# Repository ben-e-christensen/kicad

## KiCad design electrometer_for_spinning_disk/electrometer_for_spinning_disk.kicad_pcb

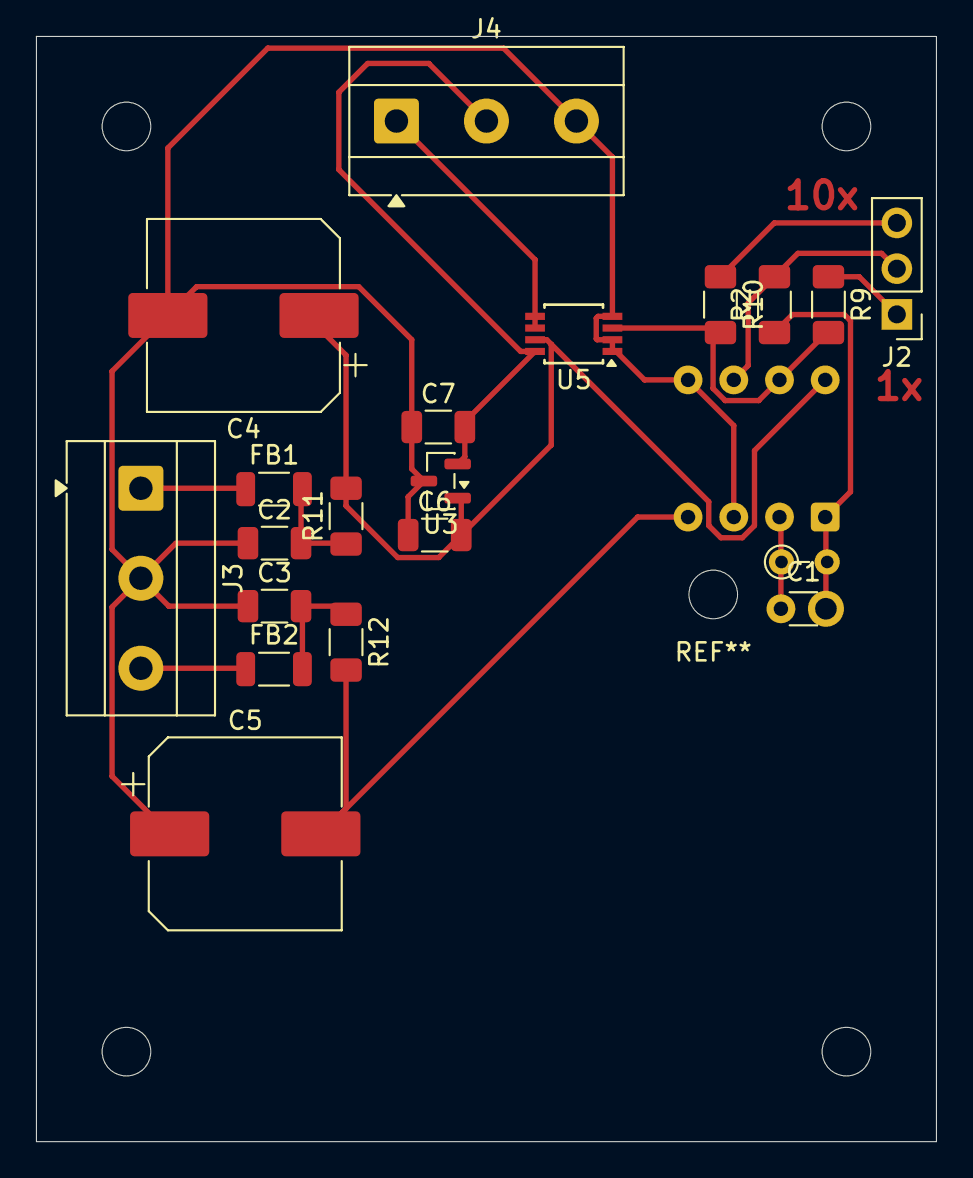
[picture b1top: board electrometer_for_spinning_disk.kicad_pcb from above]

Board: 2 copper layers, 50.0 x 61.4 mm, 21 parts (1 on the bottom side), 15 nets.

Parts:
C1: 100p; C_Disc_D3.0mm_W1.6mm_P2.50mm
C2, C3, C6, C7: 100n; C_1206_3216Metric
C4, C5: C_Polarized; CP_Elec_10x10.5
FB1, FB2: FerriteBead; L_1206_3216Metric
J2: Conn_01x03_Pin; PinHeader_1x03_P2.54mm_Vertical
J3, J4: Screw_Terminal_01x03; TerminalBlock_MetzConnect_Type055_RT01503HDWU_1x03_P5.00mm_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
R1: 5G; R_Axial_DIN0204_L3.6mm_D1.6mm_P2.54mm_Vertical
R2, R9, R11, R12: 1k; R_1206_3216Metric_Pad1.30x1.75mm_HandSolder
R10: 10k; R_1206_3216Metric_Pad1.30x1.75mm_HandSolder
U1: LMC6082; DIP-8_W7.62mm
U3: REF3025; SOT-23
U5: INA159AIDGKR; TSSOP-8_3x3mm_P0.65mm

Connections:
+2V5: C7.2, J4.2, U3.2 (OUT), U5.8 (REF_2)
+VDC: C4.1, C6.2, R11.2, U1.8 (V+), U3.1 (IN), U5.7 (V+)
-VDC: C5.2, R12.2, U1.4 (V-)
/Electro_Output: R9.2, R10.2, U1.7, U5.3 (+IN)
/Output: J4.1, U5.5 (SENSE), U5.6 (OUT)
/V+: FB1.1, J3.1
/V-: FB2.1, J3.3
GND: C2.1, C3.1, C4.2, C5.1, C6.1, C7.1, J3.2, J4.3, U1.3 (+), U1.5 (+), U3.3 (GND), U5.1 (REF_1), U5.2 (-IN), U5.4 (V-)
unnamed: C1.2, R1.2, R2.1, U1.1
unnamed: C2.2, FB1.2, R11.1
unnamed: C3.2, FB2.2, R12.1
unnamed: J2.1, R9.1
unnamed: J2.2, R2.2, U1.6 (-)
unnamed: J2.3, R10.1
unnamed: C1.1, R1.1, U1.2 (-)

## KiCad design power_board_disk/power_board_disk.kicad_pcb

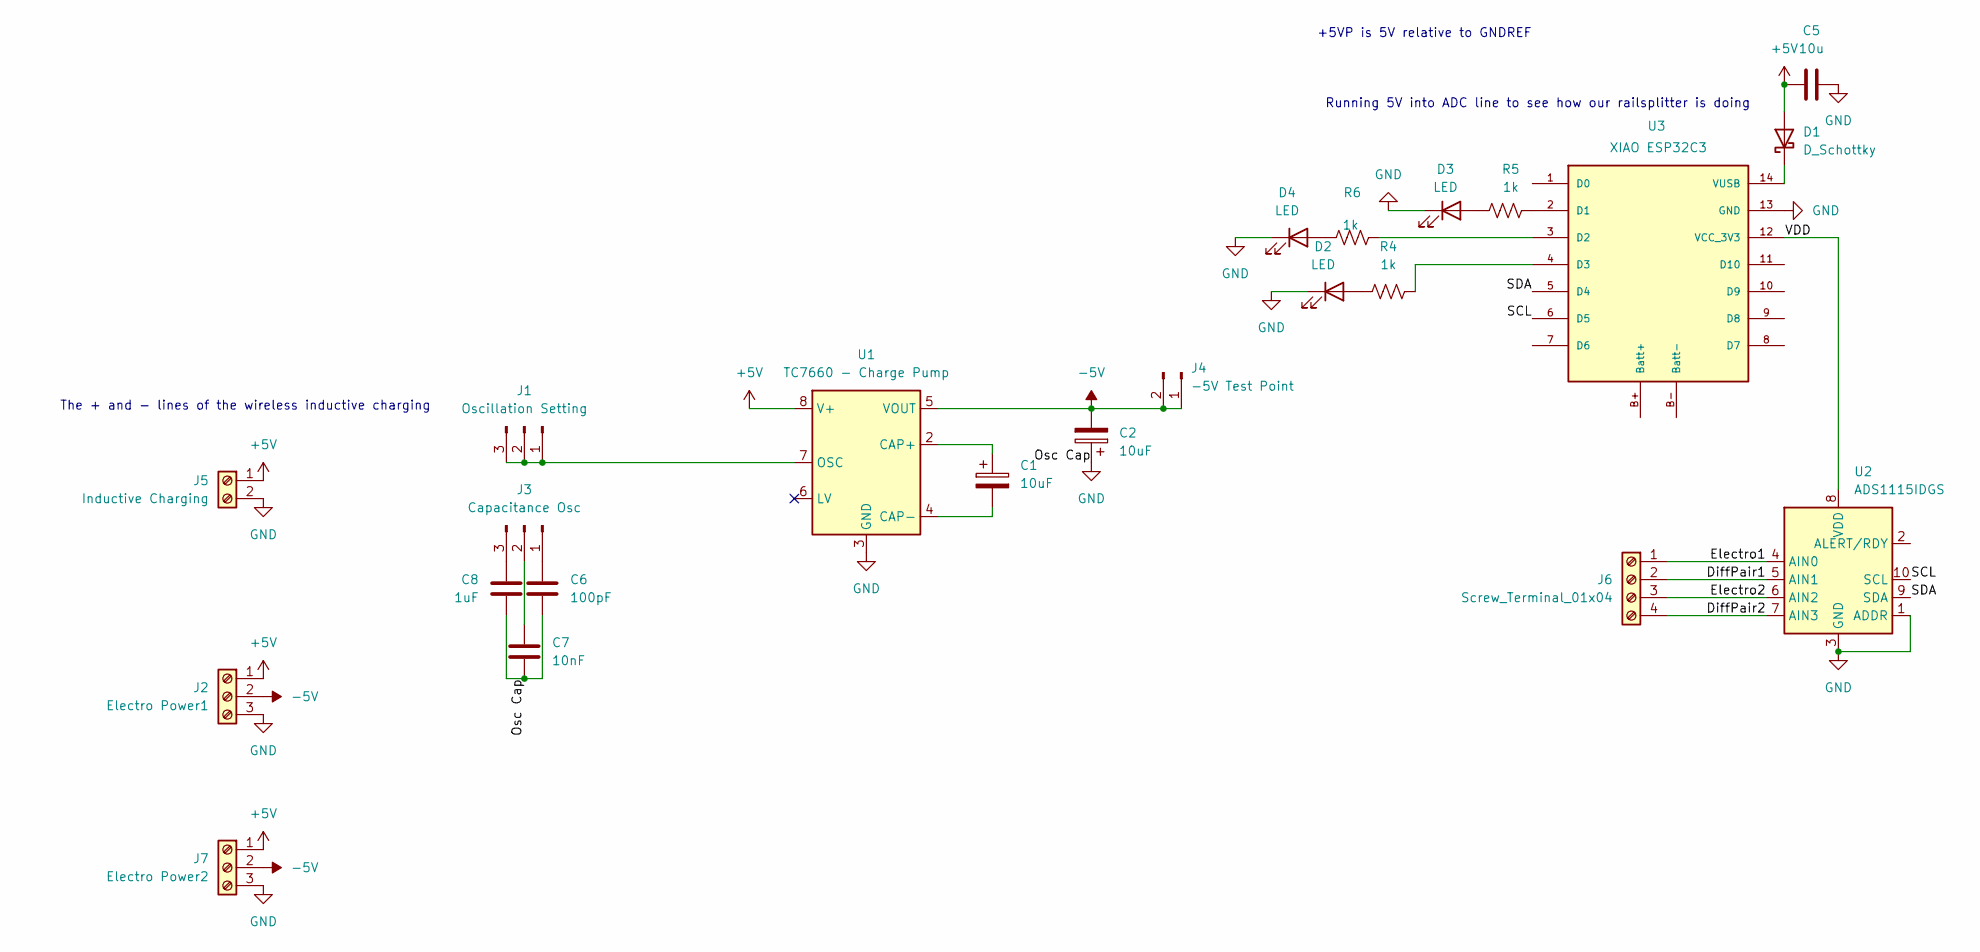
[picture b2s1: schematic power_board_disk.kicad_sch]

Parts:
C1, C2: 10uF; CP_Radial_D4.0mm_P2.00mm
C5: 10u; C_1206_3216Metric_Pad1.33x1.80mm_HandSolder
C6: 100pF; C_1206_3216Metric_Pad1.33x1.80mm_HandSolder
C7: 10nF; C_1206_3216Metric_Pad1.33x1.80mm_HandSolder
C8: 1uF; C_1206_3216Metric_Pad1.33x1.80mm_HandSolder
D1: D_Schottky; D_A-405_P7.62mm_Horizontal
D2, D3, D4: LED; LED_D1.8mm_W3.3mm_H2.4mm
J1: Oscillation Setting; PinHeader_1x03_P2.54mm_Vertical
J2: Electro Power1; TerminalBlock_MetzConnect_Type055_RT01503HDWU_1x03_P5.00mm_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
J3: Capacitance Osc; PinHeader_1x03_P2.54mm_Vertical
J4: -5V Test Point; PinHeader_1x02_P2.54mm_Vertical
J5: Inductive Charging; TerminalBlock_MaiXu_MX126-5.0-02P_1x02_P5.00mm
J6: Screw_Terminal_01x04; TerminalBlock_MetzConnect_Type055_RT01504HDWU_1x04_P5.00mm_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
J7: Electro Power2; TerminalBlock_MetzConnect_Type055_RT01503HDWU_1x03_P5.00mm_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
R4, R5, R6: 1k; R_1206_3216Metric_Pad1.30x1.75mm_HandSolder
U1: TC7660 - Charge Pump; SOIC-8_3.9x4.9mm_P1.27mm
U2: ADS1115IDGS; TSSOP-10_3x3mm_P0.5mm
U3: XIAO ESP32C3; XIAO-ESP32-C6-DIP

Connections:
+5V: C5.1, D1.2 (A), J2.1, J5.1, J7.1, U1.8 (V+)
-5V: C2.2, J2.2, J4.1, J4.2, J7.2, U1.5 (VOUT)
/DiffPair1: J6.2, U2.5 (AIN1)
/DiffPair2: J6.4, U2.7 (AIN3)
/Electro1: J6.1, U2.4 (AIN0)
/Electro2: J6.3, U2.6 (AIN2)
/SCL: U2.10 (SCL), U3.6 (D5)
/SDA: U2.9 (SDA), U3.5 (D4)
/VDD: U2.8 (VDD), U3.12 (VCC_3V3)
GND: C2.1, C5.2, C6.1, C7.1, C8.1, D2.1 (K), D3.1 (K), D4.1 (K), J2.3, J5.2, J7.3, U1.3 (GND), U2.1 (ADDR), U2.3 (GND), U3.13 (GND)
unnamed: D1.1 (K), U3.14 (VUSB)
unnamed: D2.2 (A), R4.1
unnamed: D3.2 (A), R5.1
unnamed: D4.2 (A), R6.1
unnamed: J1.1, J1.2, J1.3, U1.7 (OSC)
unnamed: C6.2, J3.1
unnamed: C7.2, J3.2
unnamed: C8.2, J3.3
unnamed: C1.1, U1.2 (CAP+)
unnamed: C1.2, U1.4 (CAP-)
unnamed: R5.2, U3.2 (D1)
unnamed: R6.2, U3.3 (D2)
unnamed: R4.2, U3.4 (D3)

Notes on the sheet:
Running 5V into ADC line to see how our railsplitter is doing
The + and - lines of the wireless inductive charging
+5VP is 5V relative to GNDREF

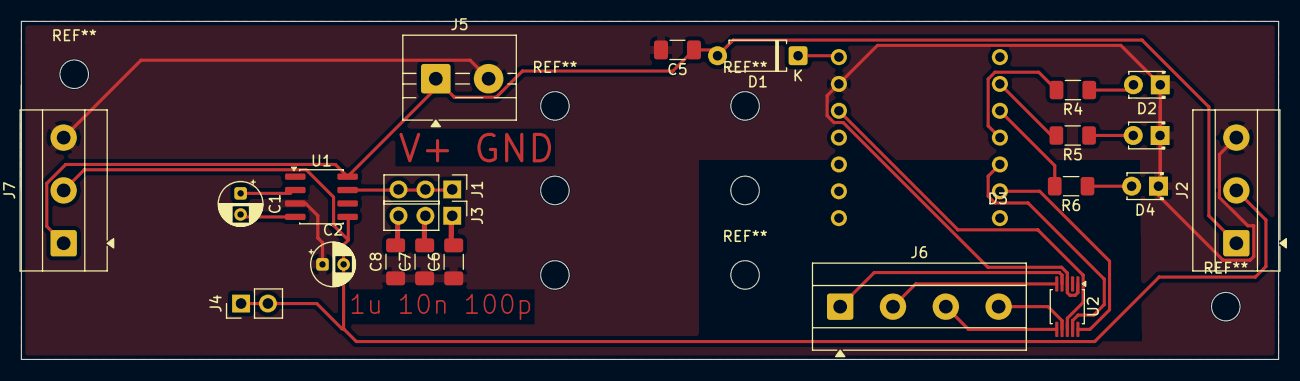
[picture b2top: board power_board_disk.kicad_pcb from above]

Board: 2 copper layers, 119.0 x 32.0 mm, 23 parts (1 on the bottom side), 23 nets.

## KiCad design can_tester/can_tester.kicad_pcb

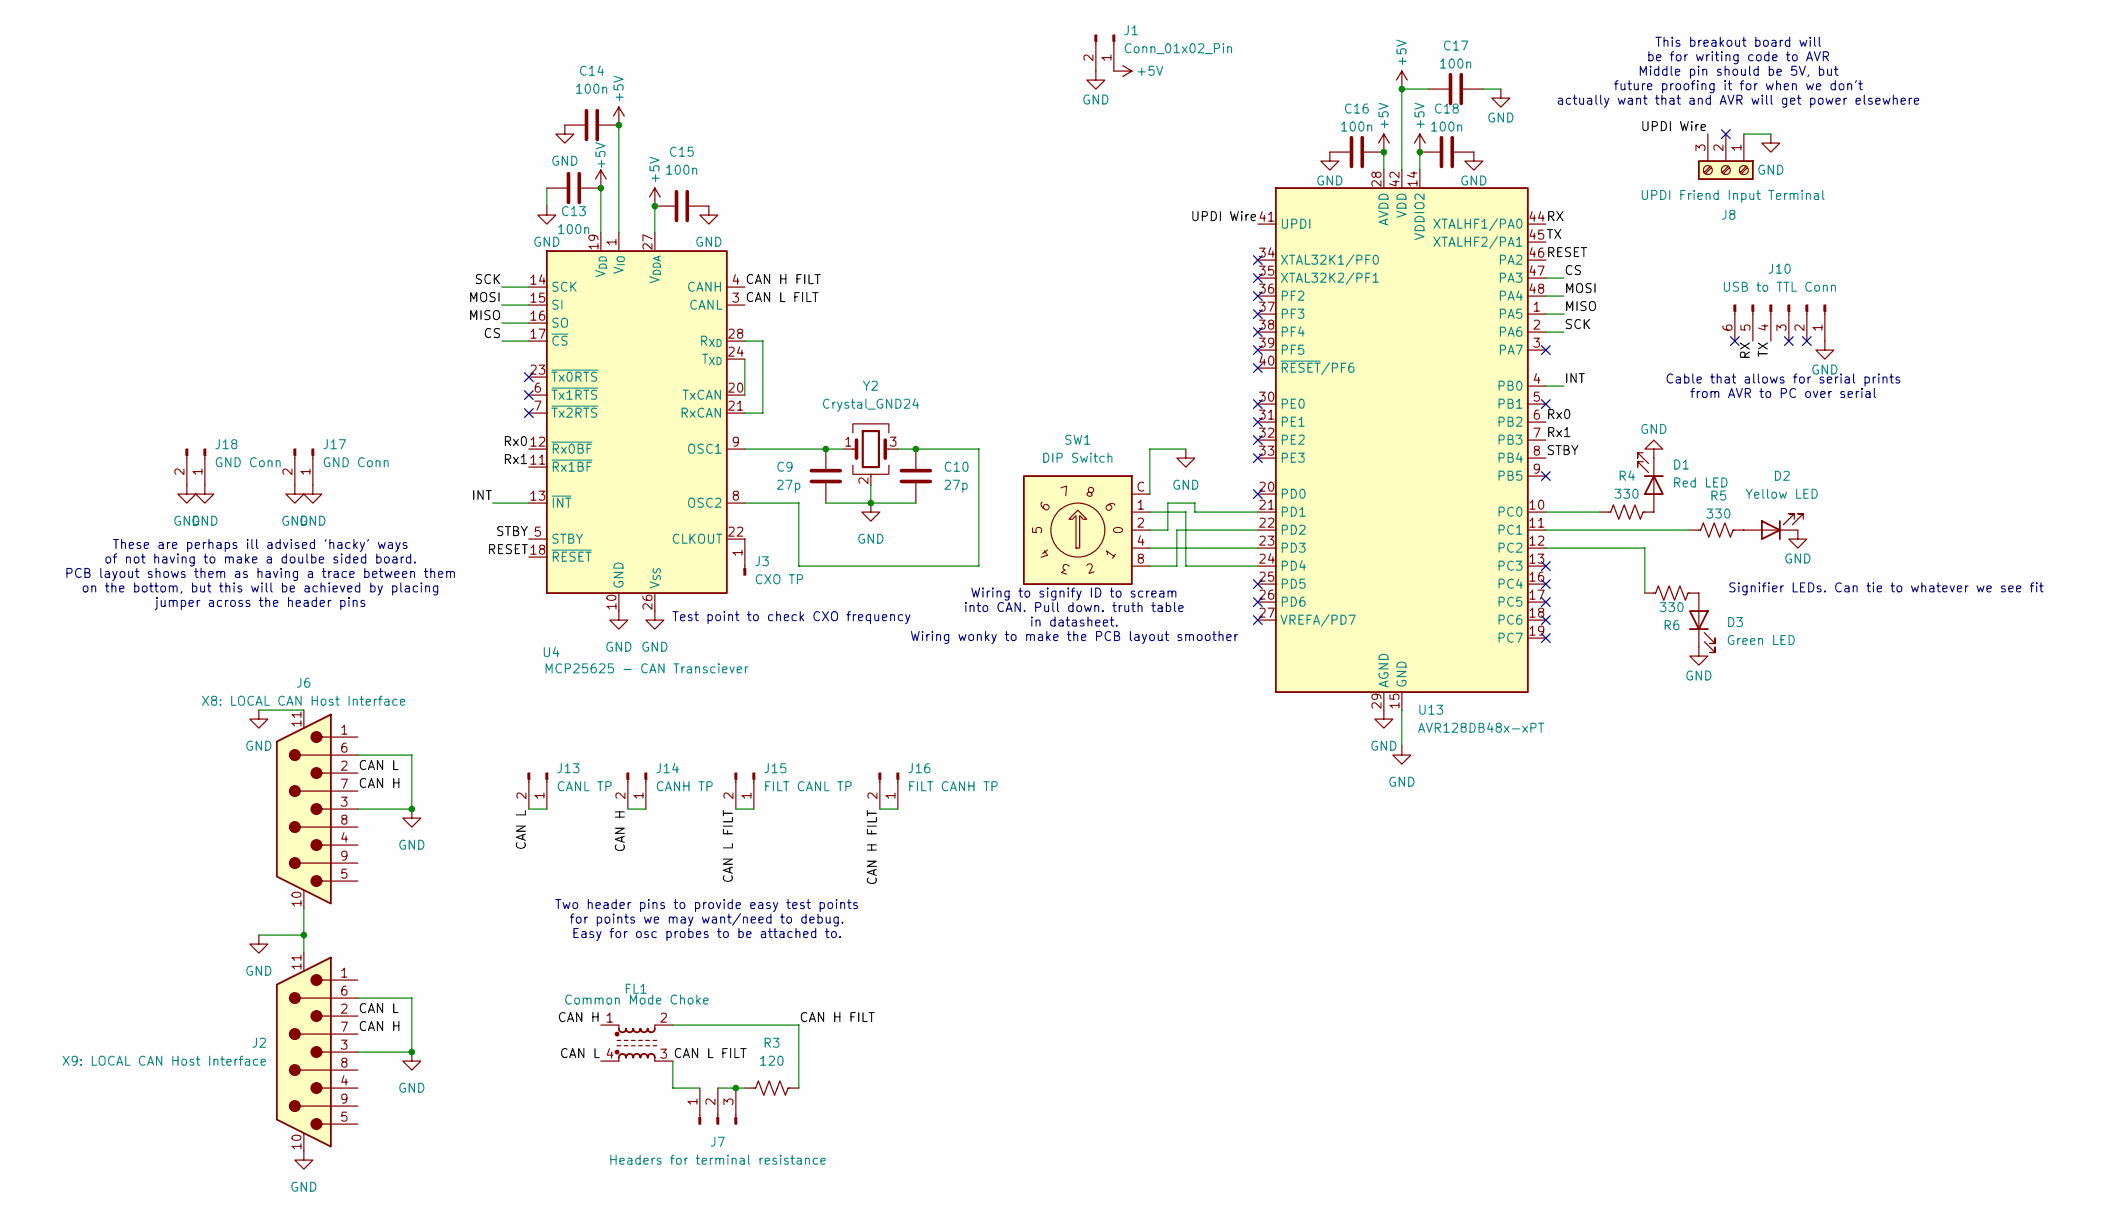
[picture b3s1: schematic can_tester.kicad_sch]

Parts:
C9, C10: 27p; C_1206_3216Metric_Pad1.33x1.80mm_HandSolder
C13, C14, C15, C16, C17, C18: 100n; C_0805_2012Metric_Pad1.18x1.45mm_HandSolder
D1: Red LED; LED_D1.8mm_W3.3mm_H2.4mm
D2: Yellow LED; LED_D1.8mm_W3.3mm_H2.4mm
D3: Green LED; LED_D1.8mm_W3.3mm_H2.4mm
FL1: Common Mode Choke; L_CommonMode_Wurth_WE-CNSW-1206
J1: Conn_01x02_Pin; TerminalBlock_MaiXu_MX126-5.0-02P_1x02_P5.00mm
J2: X9: LOCAL CAN Host Interface; CONN_DE09-SL-24_ADM_DSUB
J3: CXO TP; PinHeader_1x01_P2.54mm_Vertical
J6: X8: LOCAL CAN Host Interface; CONN_DE09-SL-24_ADM_DSUB
J7: Headers for terminal resistance; PinHeader_1x03_P2.54mm_Vertical
J8: UPDI Friend Input Terminal; TerminalBlock_MaiXu_MX126-5.0-03P_1x03_P5.00mm
J10: USB to TTL Conn; PinHeader_1x06_P2.54mm_Vertical
J13: CANL TP; PinHeader_1x02_P2.54mm_Vertical
J14: CANH TP; PinHeader_1x02_P2.54mm_Vertical
J15: FILT CANL TP; PinHeader_1x02_P2.54mm_Vertical
J16: FILT CANH TP; PinHeader_1x02_P2.54mm_Vertical
J17, J18: GND Conn; PinHeader_1x02_P2.54mm_Vertical
R3: 120; R_Axial_DIN0204_L3.6mm_D1.6mm_P2.54mm_Vertical
R4, R5, R6: 330; R_1206_3216Metric_Pad1.30x1.75mm_HandSolder
SW1: DIP Switch; Nidec_Copal_SH-7010C
U4: MCP25625 - CAN Transciever; SSOP-28_5.3x10.2mm_P0.65mm
U13: AVR128DB48x-xPT; TQFP-48_7x7mm_P0.5mm
Y2: Crystal_GND24; Crystal_SMD_3225-4Pin_3.2x2.5mm

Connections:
+5V: C13.1, C14.1, C15.1, C16.2, C17.2, C18.1, J1.1, U4.1 (V_{IO}), U4.19 (V_{DD}), U4.27 (V_{DDA}), U13.14 (VDDIO2), U13.28 (AVDD), U13.42 (VDD)
/CAN H: FL1.1, J2.7, J6.7, J14.1, J14.2
/CAN H FILT: FL1.2, J16.1, J16.2, R3.2, U4.4 (CANH)
/CAN L: FL1.4, J2.2, J6.2, J13.1, J13.2
/CAN L FILT: FL1.3, J7.1, J15.1, J15.2, U4.3 (CANL)
/CS: U4.17 (~CS), U13.47 (PA3)
/INT: U4.13 (~INT), U13.4 (PB0)
/MISO: U4.16 (SO), U13.1 (PA5)
/MOSI: U4.15 (SI), U13.48 (PA4)
/RESET: U4.18 (~RESET), U13.46 (PA2)
/RX: J10.5, U13.44 (XTALHF1/PA0)
/Rx0: U4.12 (~Rx0BF), U13.6 (PB2)
/Rx1: U4.11 (~Rx1BF), U13.7 (PB3)
/SCK: U4.14 (SCK), U13.2 (PA6)
/STBY: U4.5 (STBY), U13.8 (PB4)
/TX: J10.4, U13.45 (XTALHF2/PA1)
/UPDI Wire: J8.3, U13.41 (UPDI)
GND: C9.1, C10.1, C13.2, C14.2, C15.2, C16.1, C17.1, C18.2, D1.1 (K), D2.1 (K), D3.1 (K), J1.2, J2.3, J2.6, J2.10, J2.11, J6.3, J6.6, J6.10, J6.11, J8.1, J10.1, J17.1, J17.2, J18.1, J18.2, SW1.C, U4.10 (GND), U4.26 (V_{SS}), U13.15 (GND), U13.29 (AGND), U13.43 (GND), Y2.2 (G), Y2.4 (G)
unnamed: D1.2 (A), R4.2
unnamed: D2.2 (A), R5.2
unnamed: D3.2 (A), R6.2
unnamed: J3.1 (Pin_1_1), U4.22 (CLKOUT)
unnamed: J7.2, J7.3, R3.1
unnamed: C9.2, U4.9 (OSC1), Y2.1
unnamed: C10.2, U4.8 (OSC2), Y2.3
unnamed: U4.21 (RxCAN), U4.28 (R_{XD})
unnamed: U4.20 (TxCAN), U4.24 (T_{XD})
unnamed: R4.1, U13.10 (PC0)
unnamed: R5.1, U13.11 (PC1)
unnamed: R6.1, U13.12 (PC2)
unnamed: SW1.2, U13.21 (PD1)
unnamed: SW1.8, U13.22 (PD2)
unnamed: SW1.4, U13.23 (PD3)
unnamed: SW1.1, U13.24 (PD4)

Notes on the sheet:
Two header pins to provide easy test points for points we may want/need to debug. Easy for osc probes to be attached to.
Signifier LEDs. Can tie to whatever we see fit
This breakout board will be for writing code to AVR Middle pin should be 5V, but future proofing it for when we don't actually want that and AVR will get power elsewhere
Wiring to signify ID to scream into CAN. Pull down. truth table in datasheet. Wiring wonky to make the PCB layout smoother
Test point to check CXO frequency
These are perhaps ill advised 'hacky' ways of not having to make a doulbe sided board. PCB layout shows them as having a trace between them on the bottom, but this will be achieved by placing jumper across the header pins
Cable that allows for serial prints from AVR to PC over serial

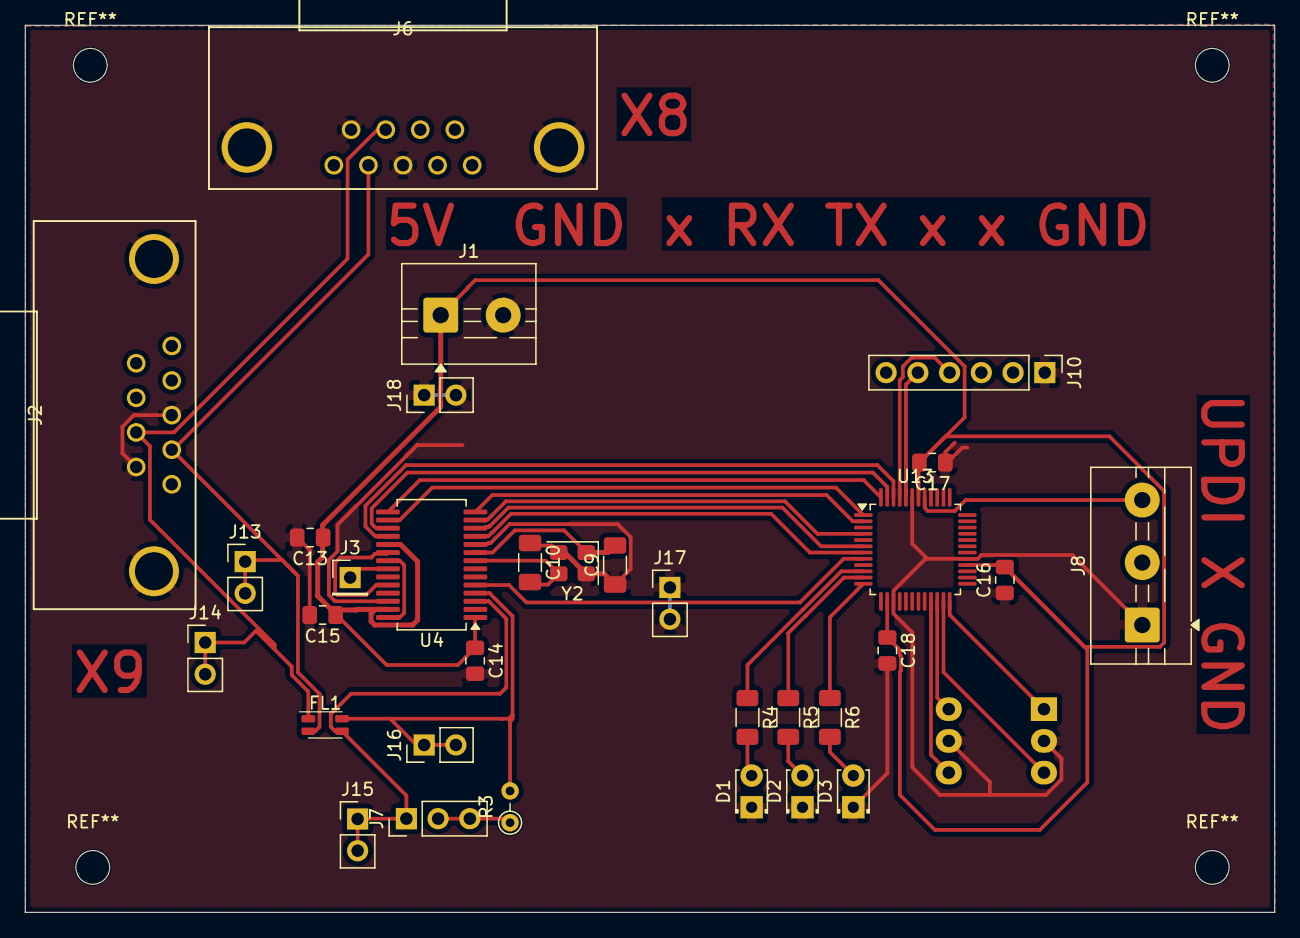
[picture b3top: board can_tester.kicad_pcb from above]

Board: 2 copper layers, 100.0 x 71.0 mm, 33 parts (1 on the bottom side), 34 nets.

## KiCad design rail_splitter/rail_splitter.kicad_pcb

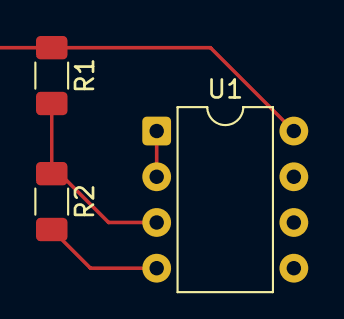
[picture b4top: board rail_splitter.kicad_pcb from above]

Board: 2 copper layers, 3 parts (0 on the bottom side), 4 nets.

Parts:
R1, R2: 10k; R_1206_3216Metric_Pad1.30x1.75mm_HandSolder
U1: LM358; DIP-8_W7.62mm

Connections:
+5V: R1.1, U1.8 (V+)
/VGND: R2.2, U1.4 (V-)
GND: U1.1, U1.2 (-)
unnamed: R1.2, R2.1, U1.3 (+)

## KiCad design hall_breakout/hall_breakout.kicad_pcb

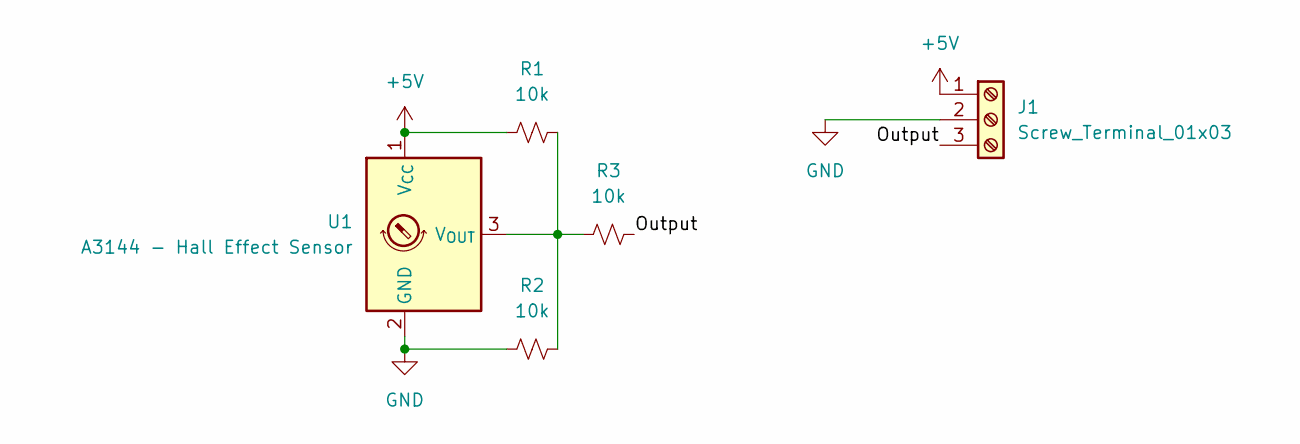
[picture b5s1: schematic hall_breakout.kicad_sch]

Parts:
J1: Screw_Terminal_01x03; TerminalBlock_Xinya_XY308-2.54-3P_1x03_P2.54mm_Horizontal
R1, R2, R3: 10k; R_1206_3216Metric_Pad1.30x1.75mm_HandSolder
U1: A3144 - Hall Effect Sensor; TO-92S

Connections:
+5V: J1.1, R1.1, U1.1 (V_{CC})
/Output: J1.3, R3.2
GND: J1.2, R2.1, U1.2 (GND)
unnamed: R1.2, R2.2, R3.1, U1.3 (V_{OUT})

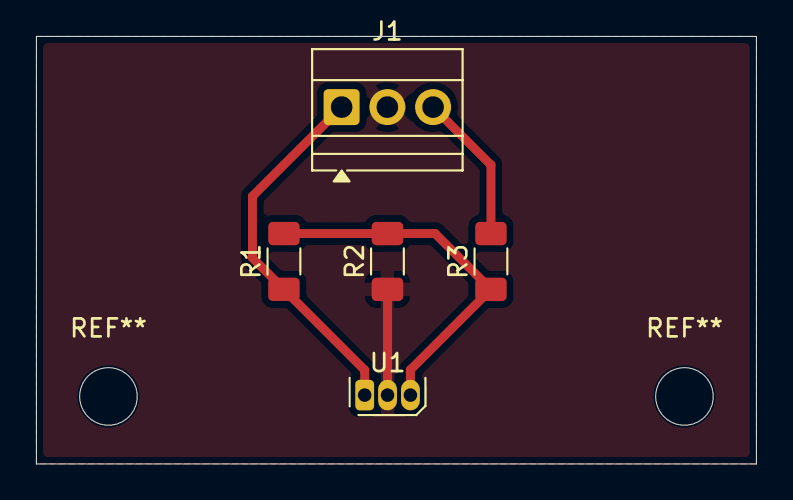
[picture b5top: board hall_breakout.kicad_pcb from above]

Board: 2 copper layers, 40.0 x 23.8 mm, 5 parts (0 on the bottom side), 4 nets.

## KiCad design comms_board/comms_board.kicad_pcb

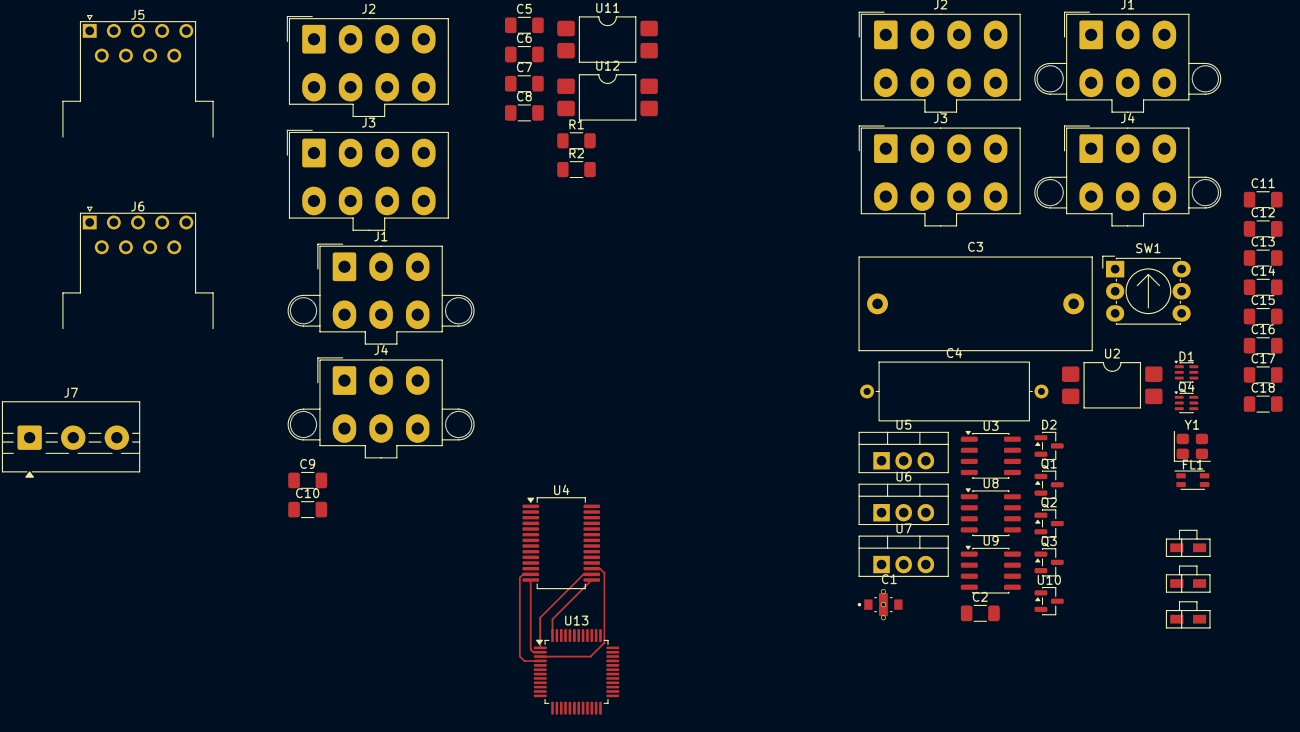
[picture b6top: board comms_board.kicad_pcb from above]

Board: 2 copper layers, 55 parts (0 on the bottom side), 22 nets.

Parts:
C1: C_Feedthrough; FIL_NFM31KC103R1H3L
C2, C9, C10: 27pF; C_1206_3216Metric_Pad1.33x1.80mm_HandSolder
C3: 10uF - Large Film Cap; C_Rect_L26.5mm_W10.5mm_P22.50mm_MKS4
C4: 100nF - Through Hole Film Cap; C_Axial_L17.0mm_D6.5mm_P20.00mm_Horizontal
C5, C6, C7, C8, C11, C12, C13, C14, C15, C16, C17, C18: 100n; C_1206_3216Metric_Pad1.33x1.80mm_HandSolder
D1: BAV199DW; SOT-363_SC-70-6
D2: BAT54S; SOT-23
D3: Green LED; Untitled
D4: Red LED; Untitled
D5: Yellow LED; Untitled
FL1: Common Mode Choke; L_CommonMode_Wurth_WE-CNSW-1206
J1, J1#2: X6; Molex_Mini-Fit_Jr_5566-06A2_2x03_P4.20mm_Vertical
J2, J2#2: X4; Molex_Mini-Fit_Jr_5566-08A_2x04_P4.20mm_Vertical
J3, J3#2: X5; Molex_Mini-Fit_Jr_5566-08A_2x04_P4.20mm_Vertical
J4, J4#2: X7; Molex_Mini-Fit_Jr_5566-06A2_2x03_P4.20mm_Vertical
J5: X9 LOCAL CAN Feedthrough Connector; DSUB-9_Pins_Horizontal_P2.77x2.84mm_EdgePinOffset9.40mm
J6: X8: LOCAL CAN Host Interface; DSUB-9_Pins_Horizontal_P2.77x2.84mm_EdgePinOffset9.40mm
J7: Pins to select 120 terminal resistance or not; TerminalBlock_MaiXu_MX126-5.0-03P_1x03_P5.00mm
Q1: MMBT3904; SOT-23
Q2: MMBT3906; SOT-23
Q3: 2N7002; SOT-23
Q4: Q_Dual_NPN_NPN_E1B1C2E2B2C1; SOT-363_SC-70-6
R1, R2: 10k; R_1206_3216Metric_Pad1.30x1.75mm_HandSolder
SW1: DIP Switch; Nidec_Copal_SH-7010C
U2, U11, U12: LTV-817S; SMDIP-4_W9.53mm
U3: INA826; SOIC-8_3.9x4.9mm_P1.27mm
U4: MCP25625 - CAN Transciever; SSOP-28_5.3x10.2mm_P0.65mm
U5: L7812 +12V Lin Reg; TO-220-3_Vertical
U6: L7912 -12V Lin Reg; TO-220-3_Vertical
U7: L7805 +5V Lin Reg; TO-220-3_Vertical
U8: OPA2140; SOIC-8_3.9x4.9mm_P1.27mm
U9: LM358; SOIC-8_3.9x4.9mm_P1.27mm
U10: REF3040 4.096 Ref Voltage; SOT-23
U13: AVR128DB48x-xPT; TQFP-48_7x7mm_P0.5mm
Y1: 16MHz CXO; Crystal_SMD_3225-4Pin_3.2x2.5mm

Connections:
+5V: C12.1, C13.1, C14.1, C15.1, C16.2, C17.2, C18.1, J2.2, U4.1 (V_{IO}), U4.19 (V_{DD}), U4.27 (V_{DDA}), U7.3 (OUT), U13.14 (VDDIO2), U13.28 (AVDD), U13.42 (VDD)
+15V: C11.1, J2.6, U7.1 (IN)
/CAN H: FL1.1, J5.7, J6.7
/CAN H FILT: FL1.2, U4.4 (CANH)
/CAN L: FL1.4, J5.2, J6.2
/CAN L FILT: FL1.3, J7.1, U4.3 (CANL)
/CS: U4.17 (~CS), U13.3 (PA7)
/INT: U4.13 (~INT), U13.4 (PB0)
/Indicator Lights/+5V: R1.1, R2.1
/Indicator Lights/HV1 RETURN: C5.2, U11.2
/Indicator Lights/HV1_ON/: C6.1, C8.1, R1.2, R2.2, U11.4, U12.4
/Indicator Lights/HV2 RETURN: C7.2, U12.2
/MISO: U4.16 (SO), U13.1 (PA5)
/MOSI: U4.15 (SI), U13.48 (PA4)
/SCK: U4.14 (SCK), U13.2 (PA6)
GND: C6.2, C8.2, C9.2, C10.1, C11.2, C12.2, C13.2, C14.2, C15.2, C16.1, C17.1, C18.2, J5.3, J5.6, J6.3, J6.6, U4.5 (STBY), U7.2 (GND), U11.3, U12.3, U13.15 (GND), U13.29 (AGND), U13.43 (GND), Y1.2 (GND), Y1.4 (GND)
GND1: J2.1, J2.3, J2.7
unnamed: J7.2, J7.3
unnamed: C10.2, U4.9 (OSC1), Y1.1 (IN)
unnamed: C9.1, U4.8 (OSC2), Y1.3 (OUT)
unnamed: U4.21 (RxCAN), U4.28 (R_{XD})
unnamed: U4.20 (TxCAN), U4.24 (T_{XD})

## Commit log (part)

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2025-09-30 Initial commit from another folder.
2025-09-30 all of them thangs at once
2025-12-30 updated pcb layout slightly
2025-12-30 slight changes to adc board
2026-06-21 committing new electro design: :
2026-06-21 added board for inductor probe/gitignore to ignore those pesky history folders
2026-06-23 committing before pull. changed size of electrometer board
2026-06-23 added to gitignore to ignore fab output files. also added empty comms board
2026-06-23 finished placing all current components into the circuit schematic. No orginization done whatsoever
2026-06-25 more changes to comms board
2026-06-29 finished comms test board?
2026-06-29 can tester board complete?:
